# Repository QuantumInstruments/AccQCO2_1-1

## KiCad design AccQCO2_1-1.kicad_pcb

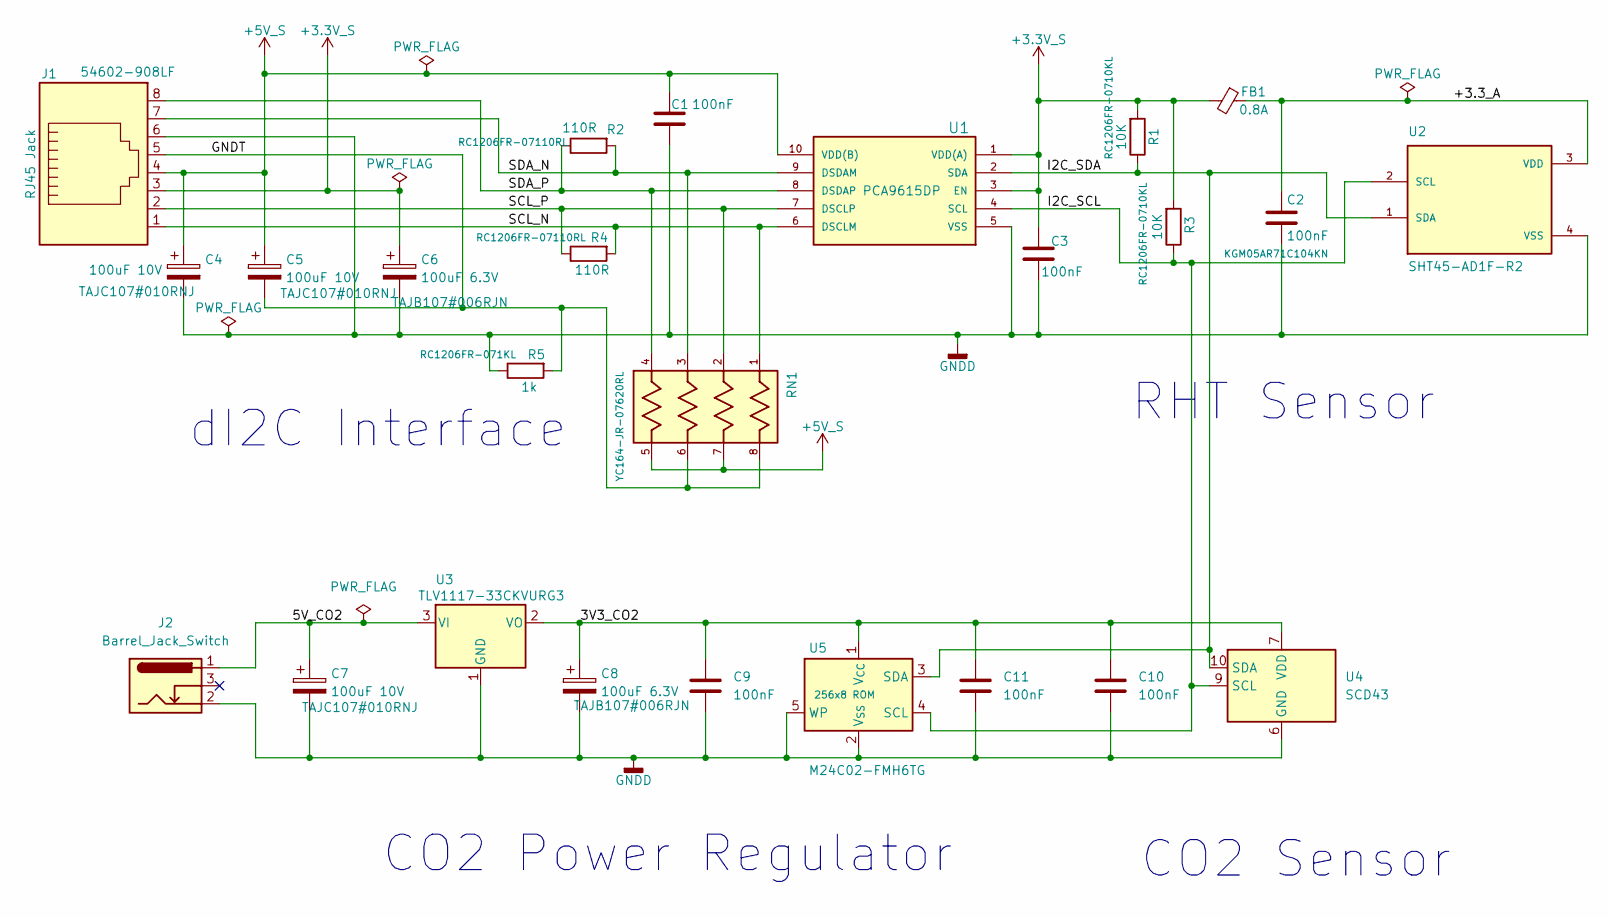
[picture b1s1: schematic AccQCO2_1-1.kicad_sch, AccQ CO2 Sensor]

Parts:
C1, C3, C9, C10, C11: 100nF; C_0805_2012Metric_Pad1.18x1.45mm_HandSolder
C2: 100nF; C_0402_1005Metric_Pad0.74x0.62mm_HandSolder; PartNo KGM05AR71C104KN
C4, C5, C7: 100uF 10V; CP_EIA-6032-28_Kemet-C_HandSolder; PartNo TAJC107#010RNJ
C6, C8: 100uF 6.3V; CP_EIA-3528-21_Kemet-B_HandSolder; PartNo TAJB107#006RJN
FB1: 0.8A; R_0603_1608Metric; PartNo MPZ1608S102ATA00
J1: RJ45 Jack; AMPHENOL_54602-908LF; PartNo 54602-908LF
J2: Barrel_Jack_Switch; CUI_PJ-102; PartNo PJ-102A
R1, R3: 10K; R_1206_3216Metric_Pad1.30x1.75mm_HandSolder; PartNo RC1206FR-0710KL
R2, R4: 110R; R_1206_3216Metric_Pad1.30x1.75mm_HandSolder; PartNo RC1206FR-07110RL
R5: 1k; R_1206_3216Metric_Pad1.30x1.75mm_HandSolder; PartNo RC1206FR-071KL
RN1: YC164-JR-07620RL; R_Array_Convex_4x0603; PARTREV 0
U1: PCA9615DP; TSSOP-10_3x3mm_P0.5mm; PartNo PCA9615DPZ
U2: SHT45-AD1F-R2; SHT4X; PartNo SHT45-AD1F-R2
U3: TLV1117-33CKVURG3; TO-252-2
U4: SCD43; Sensirion_SCD4x-1EP_10.1x10.1mm_P1.25mm_EP4.8x4.8mm; PartNo SHT45-AD1F-R2
U5: 256x8 ROM; IC_M24128-BFMH6TG; PartNo M24C02-FMH6TG

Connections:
+3.3V_S: C3.1, C6.1, FB1.2, J1.3, R1.2, R3.2, U1.1 (VDD(A)), U1.3 (EN)
+5V_S: C1.1, C4.1, C5.1, J1.4, RN1.5, RN1.7, U1.10 (VDD(B))
/3V3_CO2: C8.1, C9.1, C10.1, C11.1, U3.2 (VO), U4.7 (VDD), U4.19 (VDD), U5.1 (V_{CC})
/5V_CO2: C7.1, J2.1, U3.3 (VI)
/+3.3_A: C2.1, FB1.1, U2.3 (VDD)
/GNDT: C5.2, J1.5, R5.2, RN1.6, RN1.8
/I2C_SCL: R3.1, U1.4 (SCL), U2.2 (SCL), U4.9 (SCL), U5.4 (SCL)
/I2C_SDA: R1.1, U1.2 (SDA), U2.1 (SDA), U4.10 (SDA), U5.3 (SDA)
/SCL_N: J1.1, R4.2, RN1.1, U1.6 (DSCLM)
/SCL_P: J1.2, R4.1, RN1.2, U1.7 (DSCLP)
/SDA_N: J1.7, R2.2, RN1.3, U1.9 (DSDAM)
/SDA_P: J1.8, R2.1, RN1.4, U1.8 (DSDAP)
GNDD: C1.2, C2.2, C3.2, C4.2, C6.2, C7.2, C8.2, C9.2, C10.2, C11.2, J1.6, J2.2, R5.1, U1.5 (VSS), U2.4 (VSS), U3.1 (GND), U4.6 (GND), U4.20 (GND), U4.21 (GND), U5.2 (V_{SS}), U5.5 (WP)

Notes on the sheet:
dI2C Interface
RHT Sensor
CO2 Power Regulator
CO2 Sensor

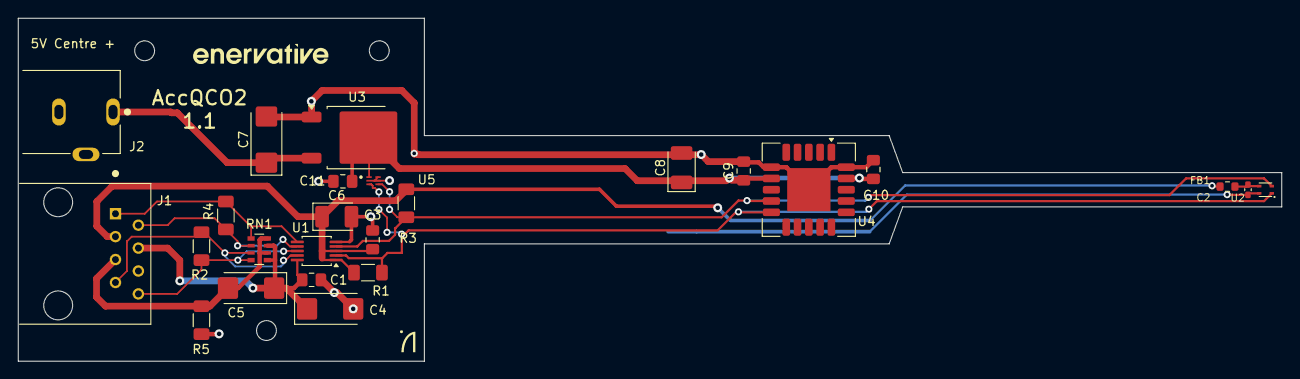
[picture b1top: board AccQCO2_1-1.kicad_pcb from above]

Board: 2 copper layers, 140.0 x 38.0 mm, 29 parts (0 on the bottom side), 13 nets.

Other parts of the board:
L: LOGO; QI_logo2-5
MH1, MH1#2, MH3: MountingHole_2.2mm_M2

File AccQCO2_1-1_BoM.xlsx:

Enervative AccQ CO2 Board BoM V1.1 - 2026-10-26
Designator | Quantity | Value | Footprint | Mount Type | PartNo | Manufacturer | Description | Comments
C1, C3, C9, C10, C11 | 5 | 100nF 50V X7R | C_0805_2012Metric_Pad1.18x1.45mm_HandSolder | smt |  | Generic | MLCC Capacitor X7R
C2 | 1 | 100nF 16V X7R | C_0402_1005Metric_Pad0.74x0.62mm_HandSolder | smt |  | Generic | MLCC Capacitor X7R | Note small footprint Part equivalent to Kyocera AVX KGM05AR71C104KN
C4, C5, C7 | 3 | 100uF 10V | CP_EIA-6032-28_Kemet-C_HandSolder | smt |  | Generic | Tantalum Capacitor | 10% or 20% Tolerance acceptable
C6, C8 | 2 | 100uF 6.3V | CP_EIA-3528-21_Kemet-B_HandSolder | smt |  | Generic | Tantalum Capacitor | 10% or 20% Tolerance acceptable
FB1 | 1 | 0.8A | R_0603_1608Metric | smt | MPZ1608S102ATA00 | TDK | Ferrite bead
J1 | 1 | RJ45 JACK | AMPHENOL_54602-908LF | tht | 54602-908LF | Amphenol | RJ45 connector, 8P8C w/o LED & Magnetics
J2 | 1 | Barrel_Jack_Switch | CUI_PJ-102 | tht | PJ-102A | Same Sky | DC Barrel Jack with an internal switch | China sourced equivalent OK
R1, R3 | 2 | 10K | R_1206_3216Metric_Pad1.30x1.75mm_HandSolder | smt |  | Generic | Resistor 1% 0.25W
R2, R4 | 2 | 110R | R_1206_3216Metric_Pad1.30x1.75mm_HandSolder | smt |  | Generic | Resistor 1% 0.25W
R5 | 1 | 1K | R_1206_3216Metric_Pad1.30x1.75mm_HandSolder | smt |  | Generic | Resistor 1% 0.25W
RN1 | 1 | 4 x 620R | R_Array_Convex_4x0603 | smt | YC164-JR-07620RL | Yageo | ±5% 62.5mW Power Per Element Isolated 4 Resistor Network | China sourced equivalent OK
U1 | 1 | PCA9615DP | TSSOP-10_3x3mm_P0.5mm | smt | PCA9615DPZ | NXP | Buffer, ReDriver 2 Channel 400kHz 10-TSSOP
U2 | 1 | SHT45-AD1F-R2 | SHT4X | smt | SHT45-AD1F-R2 | Sensirion | Digital Relative Humidity Temperature Sensor, ±1.0 %RH, ±0.1 °C, Ultra-Low-Powe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
U3 | 1 | TLV1117-33CKVURG3 | TO-252-2 | smt | TLV1117-33CKVURG3 | Texas | LDO 800mA Linear Regulator, Fixed Output, TO-252 | Alternative Parts: Diodes Incorporated: AZ1117D-3.3TRE1 STMicroelectronics: LD1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
U4 | 1 | SCD43 | Sensirion_SCD4x-1EP_10.1x10.1mm_P1.25mm_EP4.8x4.8mm | smt | SCD43-D-R2 | Sensirion | Photoacoustic CO2 sensor, 40 000 ppm, I2C, 2.4-5.5 V, Base accuracy 400 - 2000 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
U5 | 1 | 256x8 ROM | IC_M24128-BFMH6TG | smt | M24C02-FMH6TG | ST Microelectronics | I2C Serial EEPROM, 2Kb, UFDFPN5
Total Parts | 25 |  | Total number of types | 16
Total SMT | 23 |  | Total SMT types | 14
Total THT | 2 |  | Total THT types | 2
